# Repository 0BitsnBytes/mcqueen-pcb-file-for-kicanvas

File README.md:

# mcqueen-pcb-file-for-kicanvas

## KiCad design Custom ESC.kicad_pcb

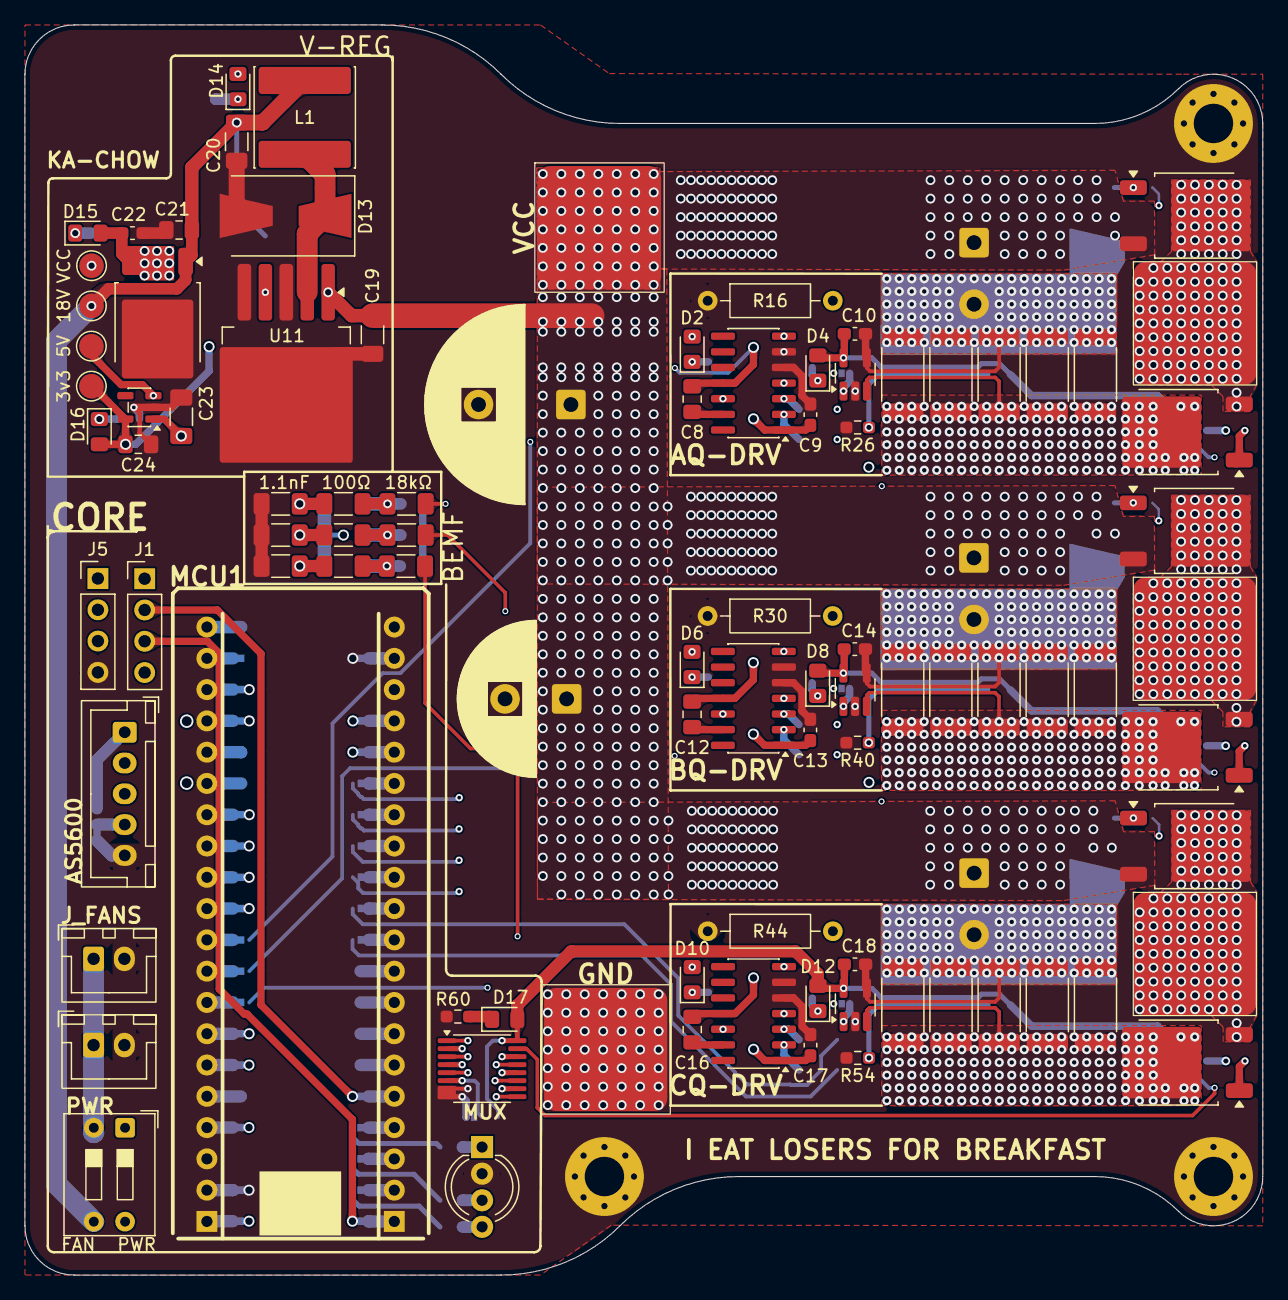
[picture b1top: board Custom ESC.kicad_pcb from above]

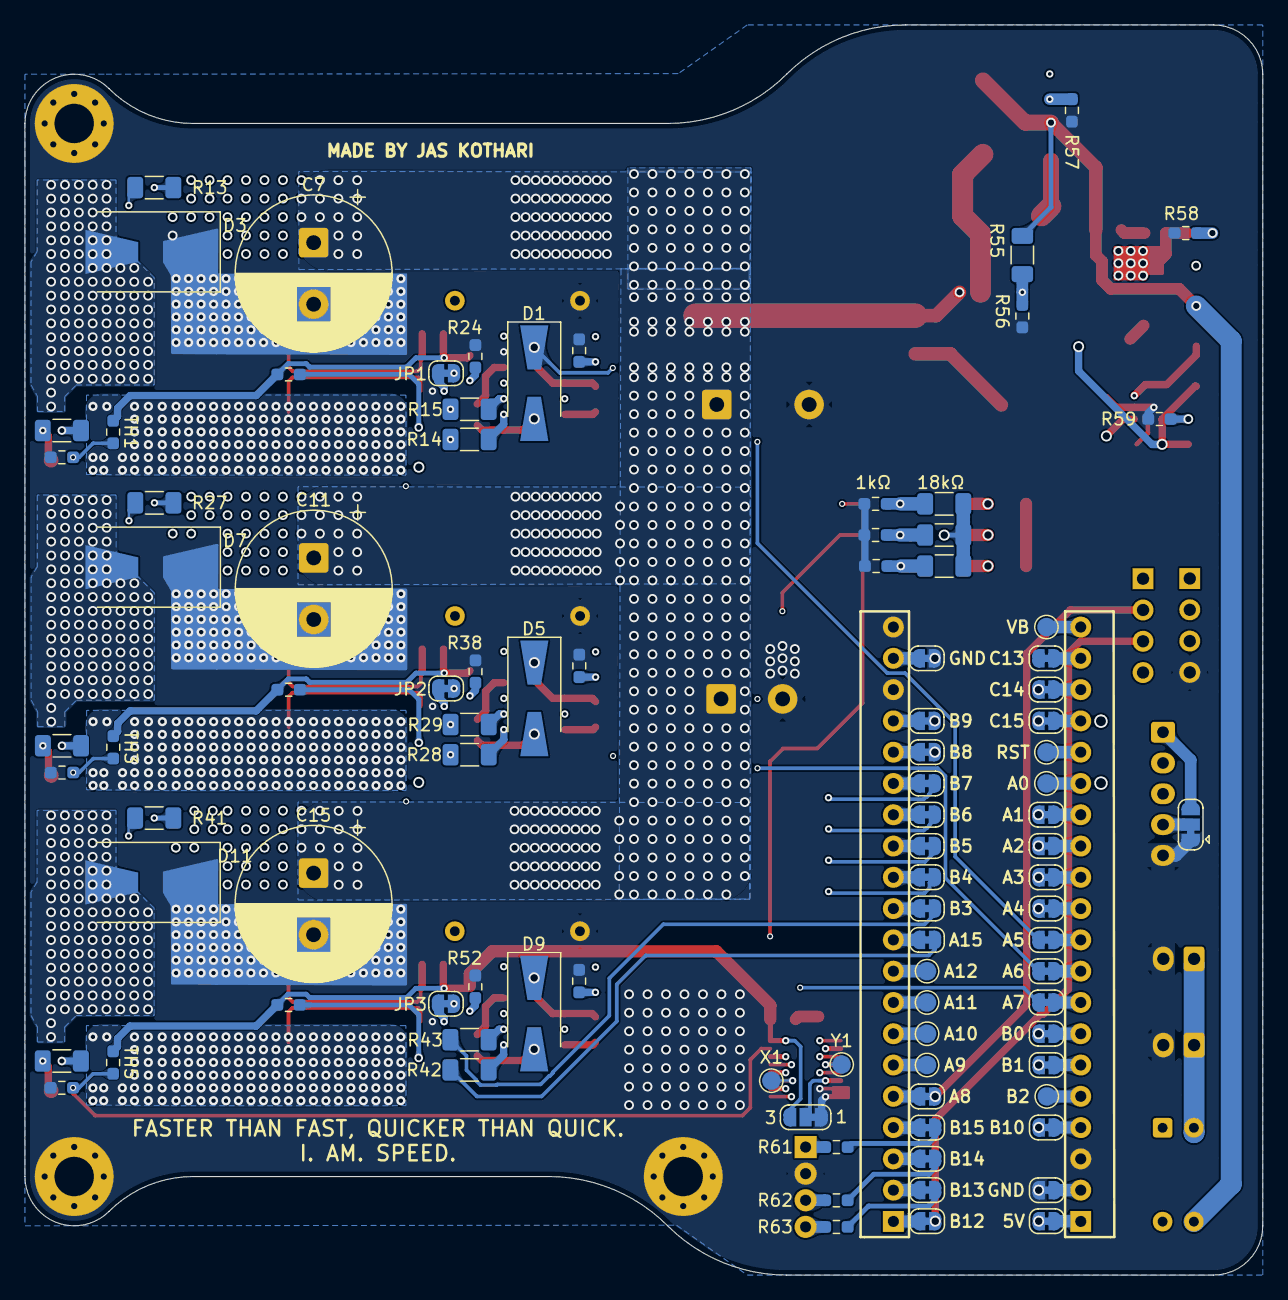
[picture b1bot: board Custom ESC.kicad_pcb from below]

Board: 6 copper layers, 100.5 x 101.5 mm, 187 parts (94 on the bottom side), 130 nets.

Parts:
3V1, 5V1, 18V1: TestPoint; TestPoint_Pad_D2.0mm
A1: OUPUT; 10x10
B1: OUPUT; 10x10
C1: OUPUT; 10x10
C2: 1000uf; CP_Radial_D16.0mm_P7.50mm
C3: 10uf; CP_Radial_D12.5mm_P5.00mm
C4, C5, C6: 1.1nF; R_1206_3216Metric_Pad1.30x1.75mm_HandSolder
C7, C11, C15: C_Polarized_Small; CP_Radial_D12.5mm_P5.00mm
C8, C12, C16, C24: 0.47uF; C_0805_2012Metric_Pad1.18x1.45mm_HandSolder
C9, C10, C13, C14, C17, C18, C22: 0.1uF; C_0603_1608Metric_Pad1.08x0.95mm_HandSolder
C19: 470uF; R_1206_3216Metric_Pad1.30x1.75mm_HandSolder
C20: 220uF; R_1206_3216Metric_Pad1.30x1.75mm_HandSolder
C21: 0.33uF; C_0805_2012Metric_Pad1.18x1.45mm_HandSolder
C23: 1uF; C_1206_3216Metric_Pad1.33x1.80mm_HandSolder
D1, D5, D9: ES1C; D_SMA-SMB_Universal_Handsoldering
D2, D4, D6, D8, D10, D12, D14, D15, D16, D17: LED_Small_Filled; LED_0805_2012Metric_Pad1.15x1.40mm_HandSolder
D3, D7, D11: D_TVS_Filled; D_SMB-SMC_Universal_Handsoldering
D13: SS34; D_SMB-SMC_Universal_Handsoldering
D18: LED_RAGB; LED_D5.0mm-4_RGB_Wide_Pins
GND: GND; 10x10
J1, J5: Conn_01x04_Pin; PinHeader_1x04_P2.54mm_Vertical
J2, J4: Conn_01x02_Socket; JST_XH_B2B-XH-A_1x02_P2.50mm_Vertical
J3: Conn_01x05_Pin; JST_XH_B5B-XH-A_1x05_P2.50mm_Vertical
JP1, JP2, JP3, JP4, JP5, JP6, JP7, JP8, JP9, JP10, JP11, JP12, JP13, JP14, JP15, JP16, JP17, JP18, JP19, JP20, JP21, JP22, JP23, JP25, JP26, JP27, JP28, JP29, JP30, JP31, JP32, JP33: SolderJumper_2_Bridged; SolderJumper-2_P1.3mm_Bridged_RoundedPad1.0x1.5mm
JP24: SolderJumper_3_Bridged12; SolderJumper-3_P1.3mm_Bridged12_RoundedPad1.0x1.5mm_NumberL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
JP34: SolderJumper_3_Bridged12; SolderJumper-3_P1.3mm_Bridged12_RoundedPad1.0x1.5mm
L1: 68uH; L_Changjiang_FNR8040S
MCU1: U?; STM32F4x1CxU6 WeActStudio
Q1, Q2, Q3, Q4, Q5, Q6: DMT10H009LK3-13; TO-252-2
R1, R2, R3, R5, R7, R9: 18kΩ; R_1206_3216Metric_Pad1.30x1.75mm_HandSolder
R4, R6, R8, R14, R15, R28, R29, R42, R43: 100Ω; R_1206_3216Metric_Pad1.30x1.75mm_HandSolder
R10, R11, R12, R56: 1kΩ; R_0603_1608Metric_Pad0.98x0.95mm_HandSolder
R13, R17, R27, R31, R41, R45: 10Ω; R_1206_3216Metric_Pad1.30x1.75mm_HandSolder
R16, R30, R44: THT; R_Axial_DIN0207_L6.3mm_D2.5mm_P10.16mm_Horizontal
R18, R24, R32, R38, R46, R52, R57, R58, R59, R60, R61: 330Ω; R_0603_1608Metric_Pad0.98x0.95mm_HandSolder
R19, R20, R21, R22, R23, R33, R34, R35, R36, R37, R47, R48, R49, R50, R51: 5mΩ; R_2512_6332Metric_Pad1.40x3.35mm_HandSolder
R25, R26, R39, R40, R53, R54: 10kΩ; R_0603_1608Metric_Pad0.98x0.95mm_HandSolder
R55: 14kΩ; R_1206_3216Metric_Pad1.30x1.75mm_HandSolder
R62: 470Ω; R_0603_1608Metric_Pad0.98x0.95mm_HandSolder
R63: 47Ω; R_0603_1608Metric_Pad0.98x0.95mm_HandSolder
SW1: SW_DIP_x02; SW_DIP_SPSTx02_Slide_9.78x7.26mm_W7.62mm_P2.54mm
TH1, TH2, TH3, TH4, TH5, TH6: NCU18XH103F6SRB; R_0603_1608Metric_Pad0.98x0.95mm_HandSolder
TP1, TP2, TP3, TP4, TP5, TP6, TP7, TP8: TestPoint; TestPoint_Pad_D1.5mm
U1, U3, U5: IR21084; SOIC-14_3.9x8.7mm_P1.27mm
U2, U4, U6: INA180A2; SOT-23-5_HandSoldering
U11: LM2596S-ADJ; TO-263-5_TabPin3
U14: SL78M05; TO-252-2
U15: ET52333; SOT-23-5
U16: CD4052B; TSSOP-16_4.4x5mm_P0.65mm
VCC: VCC; 10x10
VCC2: TestPoint; TestPoint_Pad_D2.0mm
X1: TestPoint; TestPoint_Pad_D1.5mm
Y1: TestPoint; TestPoint_Pad_D1.5mm

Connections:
+3V3: 3V1.1 (1_1), C10.1, C14.1, C18.1, C24.2, D4.2 (A), D8.2 (A), D12.2 (A), D16.2 (A), D17.2 (A), J3.1 (VCC), J5.1, JP24.3 (B), JP34.3 (B), TH1.1, TH2.1, TH3.1, TH4.1, TH5.1, TH6.1, U2.5 (V+), U4.5 (V+), U6.5 (V+), U15.5 (VOUT), U16.16 (VDD)
+5V: 5V1.1 (1_1), C22.1, C23.1, D15.2 (A), J1.1, SW1.4, U14.3 (+5V), U15.1 (VIN), U15.3 (EN)
+18V: 18V1.1 (1_1), C9.1, C13.1, C17.1, C20.1, C21.1, D1.2 (A), D2.2 (A), D5.2 (A), D6.2 (A), D9.2 (A), D10.2 (A), D14.2 (A), L1.2, R55.2, SW1.3, U1.1 (VCC), U3.1 (VCC), U5.1 (VCC), U14.1 (VIN)
/A_BEMF: C4.1, JP23.1 (A), R4.1
/A_HIN: JP25.1 (A), R14.1
/A_I: JP1.2 (B), JP17.1 (A)
/A_LIN: JP27.1 (A), R15.1
/A_PHASE: A1.1 (1_1), C8.2, D1.1 (K), D3.2 (A2), Q1.2 (S), Q2.3 (D), R5.2, U1.11 (VS)
/A_Q1: R25.1, TH1.2, U16.12 (X0)
/A_Q2: R26.1, TH2.2, U16.1 (Y0)
/B_BEMF: C5.1, JP21.1 (A), R6.1
/B_HIN: JP20.1 (A), R28.1
/B_I: JP2.2 (B), JP15.1 (A)
/B_LIN: JP22.1 (A), R29.1
/B_PHASE: B1.1 (1_1), C12.2, D5.1 (K), D7.2 (A2), Q3.2 (S), Q4.3 (D), R7.2, U3.11 (VS)
/B_Q1: R39.1, TH3.2, U16.14 (X1)
/B_Q2: R40.1, TH4.2, U16.5 (Y1)
/CORE/A8: J1.2, JP11.1 (A)
/CORE/B10: J1.4, JP10.1 (A)
/CORE/B12: J1.3, JP4.1 (A)
/CORE/BLUE: JP6.1 (A), R63.2
/CORE/GREEN: JP8.1 (A), R62.2
/CORE/MUX_A: JP30.1 (A), U16.10 (A)
/CORE/MUX_B: JP31.1 (A), U16.9 (B)
/CORE/Q1_TEMP: JP13.1 (A), U16.13 (X)
/CORE/Q2_TEMP: JP12.1 (A), U16.3 (Y)
/CORE/RED: JP9.1 (A), R61.2
/CORE/SCL: J3.2 (SCL), J5.2, JP29.1 (A)
/CORE/SDA: J3.3 (SDA), J5.3, JP28.1 (A)
/CORE/fan+: J2.1 (V+), J4.1 (V+), SW1.2
/C_BEMF: C6.1, JP19.1 (A), R8.1
/C_HIN: JP16.1 (A), R42.1
/C_I: JP3.2 (B), JP14.1 (A)
/C_LIN: JP18.1 (A), R43.1
/C_PHASE: C1.1 (1_1), C16.2, D9.1 (K), D11.2 (A2), Q5.2 (S), Q6.3 (D), R9.2, U5.11 (VS)
/C_Q1: R53.1, TH5.2, U16.15 (X2)
/C_Q2: R54.1, TH6.2, U16.2 (Y2)
GND: C2.2, C3.2, C4.2, C5.2, C6.2, C7.2, C9.2, C10.2, C11.2, C13.2, C14.2, C15.2, C17.2, C18.2, C19.2, C20.2, C21.2, C22.2, C23.2, C24.1, D3.1 (A1), D7.1 (A1), D11.1 (A1), D13.2 (A), D18.2 (A), GND.1 (1_1), J2.2 (GND), J3.5 (GND), J4.2 (GND), J5.4, JP7.1 (A), JP24.1 (A), JP32.1 (A), JP34.1 (A), R10.1, R11.1, R12.1, R16.1, R18.1, R19.2, R20.2, R21.2, R22.2, R23.2, R24.1, R25.2, R26.2, R30.1, R32.1, R33.2, R34.2, R35.2, R36.2, R37.2, R38.1, R39.2, R40.2, R44.1, R46.1, R47.2, R48.2, R49.2, R50.2, R51.2, R52.1, R53.2, R54.2, R56.1, R57.1, R58.1, R59.1, R60.1, U1.5 (VSS), U1.6 (COM), U2.2 (GND), U2.4 (-), U3.5 (VSS), U3.6 (COM), U4.2 (GND), U4.4 (-), U5.5 (VSS), U5.6 (COM), U6.2 (GND), U6.4 (-), U11.3 (GND), U11.5 (~ON/OFF), U14.2 (GND), U15.2 (GND), U16.7 (VEE), U16.8 (VSS)
unnamed: D2.1 (K), R18.2
unnamed: D4.1 (K), R24.2
unnamed: D6.1 (K), R32.2
unnamed: D8.1 (K), R38.2
unnamed: D10.1 (K), R46.2
unnamed: D12.1 (K), R52.2
unnamed: D13.1 (K), L1.1, U11.2 (OUT)
unnamed: D14.1 (K), R57.2
unnamed: D15.1 (K), R58.2
unnamed: D16.1 (K), R59.2
unnamed: D17.1 (K), R60.2
unnamed: D18.4 (BK), R63.1
unnamed: D18.3 (GK), R62.1
unnamed: D18.1 (RK), R61.1
unnamed: J3.4 (DIR), JP34.2 (C)
unnamed: JP1.1 (A), U2.1
unnamed: JP2.1 (A), U4.1
unnamed: JP3.1 (A), U6.1
unnamed: JP4.2 (B), MCU1.1 (PB12)
unnamed: JP5.1 (A), SW1.1
unnamed: JP5.2 (B), MCU1.40 (5V)
unnamed: JP6.2 (B), MCU1.2 (PB13)
unnamed: JP7.2 (B), MCU1.39 (GND)
unnamed: JP8.2 (B), MCU1.3 (PB14)
unnamed: JP9.2 (B), MCU1.4 (PB15)
unnamed: JP10.2 (B), MCU1.37 (PB10)
unnamed: JP11.2 (B), MCU1.5 (PA8)
unnamed: JP12.2 (B), MCU1.35 (PB1)
unnamed: JP13.2 (B), MCU1.34 (PB0)
unnamed: JP14.2 (B), MCU1.33 (PA7)
unnamed: JP15.2 (B), MCU1.32 (PA6)
unnamed: JP16.2 (B), MCU1.10 (PA15)
unnamed: JP17.2 (B), MCU1.31 (PA5)
unnamed: JP18.2 (B), MCU1.11 (PB3)
unnamed: JP19.2 (B), MCU1.30 (PA4)
unnamed: JP20.2 (B), MCU1.12 (PB4)
unnamed: JP21.2 (B), MCU1.29 (PA3)
unnamed: JP22.2 (B), MCU1.13 (PB5)
unnamed: JP23.2 (B), MCU1.28 (PA2)
unnamed: JP24.2 (C), U16.6 (INH)
unnamed: JP25.2 (B), MCU1.14 (PB6)
unnamed: JP26.2 (B), MCU1.27 (PA1)
unnamed: JP27.2 (B), MCU1.15 (PB7)
unnamed: JP28.2 (B), MCU1.16 (PB8)
unnamed: JP29.2 (B), MCU1.17 (PB9)
unnamed: JP30.2 (B), MCU1.24 (PC15)
unnamed: JP31.2 (B), MCU1.23 (PC14)
unnamed: JP32.2 (B), MCU1.19 (GND)
unnamed: JP33.2 (B), MCU1.22 (PC13)
unnamed: MCU1.26 (PA0), TP6.1 (1_1)
unnamed: MCU1.6 (PA9), TP2.1 (1_1)
unnamed: MCU1.7 (PA10), TP3.1 (1_1)
unnamed: MCU1.8 (PA11), TP4.1 (1_1)
unnamed: MCU1.9 (PA12), TP5.1 (1_1)
unnamed: MCU1.36 (PB2), TP1.1 (1_1)
unnamed: MCU1.25 (RST), TP7.1 (1_1)
unnamed: MCU1.21 (VBAT), TP8.1 (1_1)
unnamed: Q1.1 (G), R13.2
unnamed: Q2.1 (G), R17.2
unnamed: Q2.2 (S), R19.1, R20.1, R21.1, R22.1, R23.1, U2.3 (+)
unnamed: Q3.1 (G), R27.2
unnamed: Q4.1 (G), R31.2
unnamed: Q4.2 (S), R33.1, R34.1, R35.1, R36.1, R37.1, U4.3 (+)
unnamed: Q5.1 (G), R41.2
unnamed: Q6.1 (G), R45.2
unnamed: Q6.2 (S), R47.1, R48.1, R49.1, R50.1, R51.1, U6.3 (+)
unnamed: R1.2, R4.2, R5.1, R10.2
unnamed: R2.2, R6.2, R7.1, R11.2
unnamed: R3.2, R8.2, R9.1, R12.2
unnamed: R16.2, U1.4 (DT)
unnamed: R14.2, U1.2 (HIN)
unnamed: R13.1, U1.12 (HO)
unnamed: R17.1, U1.7 (LO)
unnamed: C8.1, U1.13 (VB)
unnamed: R15.2, U1.3 (~LIN)
unnamed: R30.2, U3.4 (DT)
unnamed: R28.2, U3.2 (HIN)
unnamed: R27.1, U3.12 (HO)
unnamed: R31.1, U3.7 (LO)
unnamed: C12.1, U3.13 (VB)
unnamed: R29.2, U3.3 (~LIN)
unnamed: R44.2, U5.4 (DT)
unnamed: R42.2, U5.2 (HIN)
unnamed: R41.1, U5.12 (HO)
unnamed: R45.1, U5.7 (LO)
unnamed: C16.1, U5.13 (VB)
unnamed: R43.2, U5.3 (~LIN)
unnamed: R55.1, R56.2, U11.4 (FB)
unnamed: U16.11 (X3), X1.1 (1_1)
unnamed: U16.4 (Y3), Y1.1 (1_1)
VCC: C2.1, C3.1, C7.1, C11.1, C15.1, C19.1, Q1.3 (D), Q3.3 (D), Q5.3 (D), U11.1 (VIN), VCC.1 (1_1), VCC2.1 (1_1)
VN: JP26.1 (A), R1.1, R2.1, R3.1

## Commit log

2026-06-12 changed files
2026-06-12 redo files
2026-06-13 redo gerber
2026-06-13 redo github
